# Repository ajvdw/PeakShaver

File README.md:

# PeakShaver

Limit charging current for EV Charger using Smart Meter Data

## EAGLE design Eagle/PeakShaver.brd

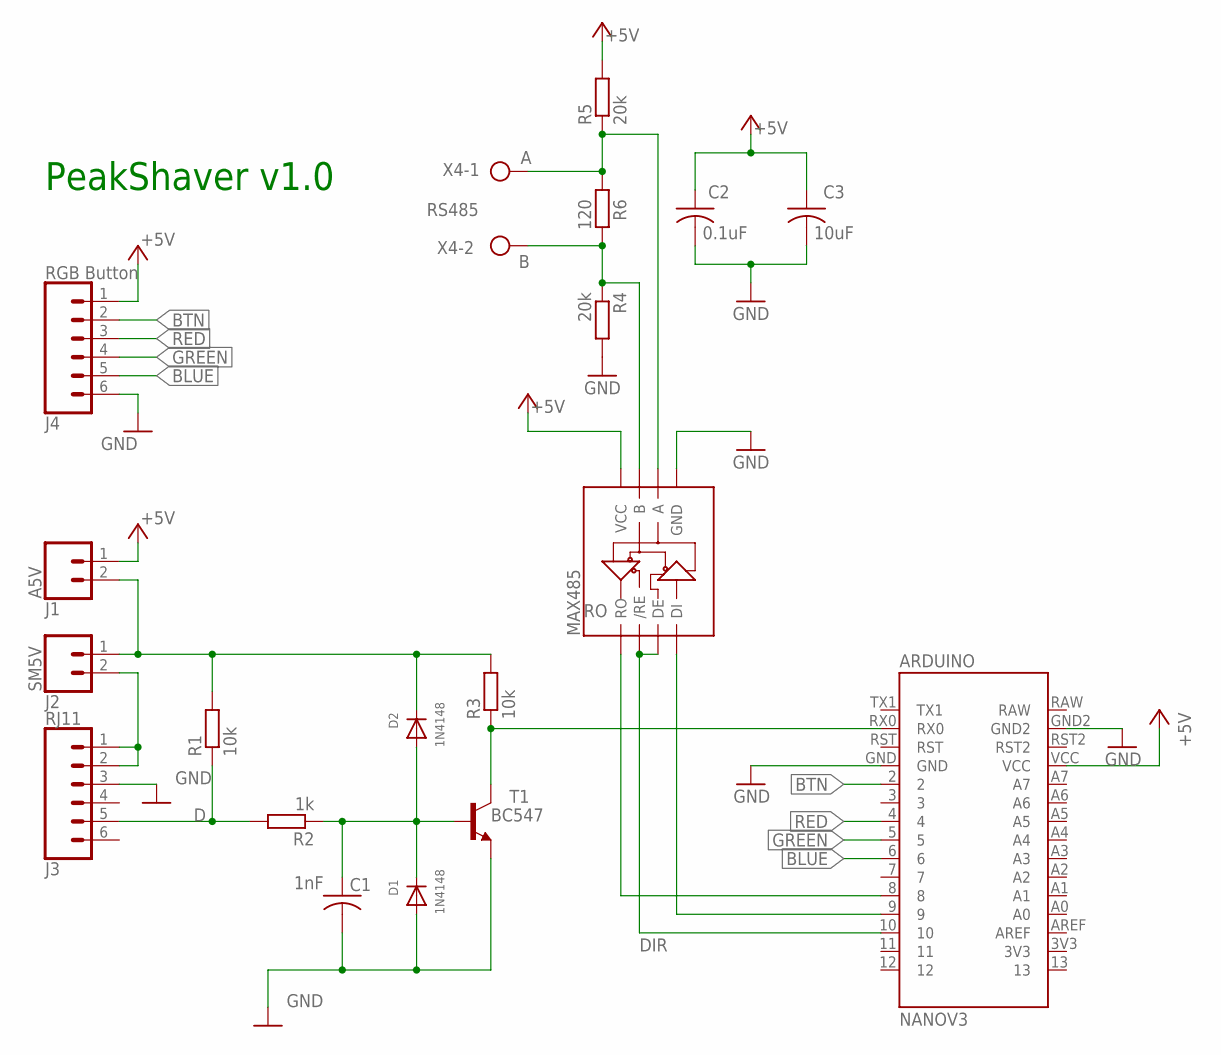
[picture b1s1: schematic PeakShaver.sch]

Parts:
ARDUINO: NANOV3
C1: 1nF; C025-025X050
C2: 0.1uF; C025-025X050
C3: 10uF; CAP_RADIAL_2MM
D1, D2: 1N4148; DO-1N4148
J1: A5V; 1X02
J2: SM5V; 1X02
J3: RJ11; RJ11-6
J4: RGB Button; 1X06_LOCK
MAX485: SPARKFUN-IC-COMMS_RS485; TEXAS_DIL08
R1, R3: 10k; 0207/10
R2: 1k; 0207/10
R4, R5: 20k; 0207/10
R6: 120; 0207/10
T1: BC547; TO92
X4: RS485; W237-102

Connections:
+5V: ARDUINO.VCC, C2.1, C3.1, J1.1, J4.1, MAX485.8 (VCC), R5.2
A: MAX485.6 (A), R5.1, R6.1, X4.1
B: MAX485.7 (B), R4.1, R6.2, X4.2
BASE: C1.1, D1.C, D2.A, R2.1, T1.2 (B)
BLUE: ARDUINO.6, J4.5
BTN: ARDUINO.2, J4.2
D: J3.5, R1.1, R2.2
DI: ARDUINO.9, MAX485.4 (DI)
DIR: ARDUINO.10, MAX485.2 (/RE), MAX485.3 (DE)
GND: ARDUINO.GND, ARDUINO.GND2, C1.2, C2.2, C3.2, D1.A, J3.3, J4.6, MAX485.5 (GND), R4.2, T1.1 (E)
GREEN: ARDUINO.5, J4.4
unnamed: D2.C, J1.2, J2.1, R1.2, R3.2
RED: ARDUINO.4, J4.3
RO: ARDUINO.8, MAX485.1 (RO)
RTS: J2.2, J3.1, J3.2
RX: ARDUINO.RX0, R3.1, T1.3 (C)

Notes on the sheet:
PeakShaver v1.0

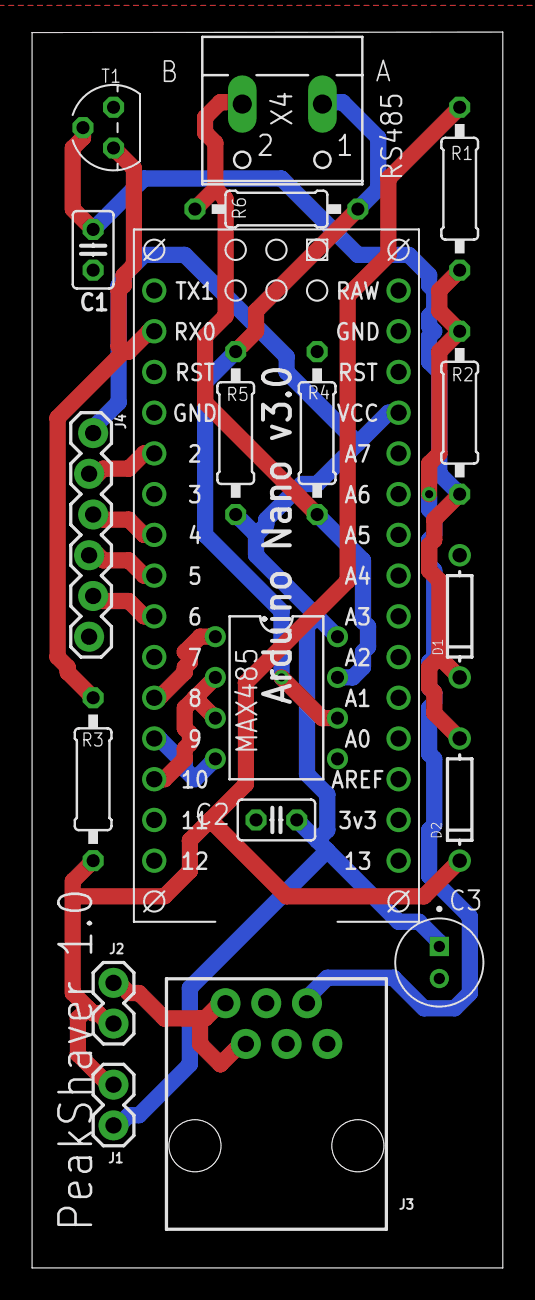
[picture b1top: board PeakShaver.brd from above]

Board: 2 copper layers, 29.4 x 77.1 mm, 19 parts (0 on the bottom side), 16 nets.

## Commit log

2020-03-24 Cleanup Code
2020-03-24 Added Media
2020-03-24 Cleanup
2020-03-24 Screenshot
2020-04-12 Optimizations
2020-04-19 fixed bug in P1 connection
    P1 ground and data line were swapped in version 0.9
2020-04-27 Minor changes

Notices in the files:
parts and their libraries:
SparkFun-Connectors: Licensing: Creative Commons ShareAlike 4.0 International - https://creativecommons.org/licenses/by-sa/4.0
